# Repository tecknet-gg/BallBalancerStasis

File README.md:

## Overview

A project where I make a cool 3RRS parallel manipulator, and throw a camera underneath and get it to balance a ball. It uses Computer Vision (CV) to locate the ball on the platform, and then the location and velocity vector will be used to calculate the pose of the platform (using Inverse Kinematics) to then push the ball back to the centre. 

I manily made this project since it seemed cool when I saw a couple of people who had made them on YouTube (https://www.youtube.com/watch?v=v4F-cGDGiEw&t=235s), and I (being masochistic), like using PID, so here we are!

The hardware for the most part is done, and the .step file can be found in the hardware folder. Firmware is still in the very early stages, and the balancing software is yet to be written.

With the custom PCB:

Here's the BOM:

| Component             | Function             | Quantity | Price (unit*qty) | Source                                                                                                                                                                     |
| --------------------- | -------------------- | -------- | ---------------- | -------------------------------------------------------------------------------------------------------------------------------------------------------------------------- |
| Raspberry Pi Zero 2 W | Microcontroller      | 1        | £14.15           | https://shop.pimoroni.com/products/raspberry-pi-zero-2-w?variant=42101934587987                                                                                            |
| Pi Camera             | Camera               | 1        | £7               | https://www.amazon.co.uk/dp/B0BZVP3SQW                                                                                                                                     |
| Pi Zero Accessories   | Assorted Accessories | 1        | £8               | https://shop.pimoroni.com/products/zero-adaptor-kit?variant=10462230279 & https://shop.pimoroni.com/products/camera-cable-raspberry-pi-zero-edition?variant=32092803891283 |
| Tie Rod               | Joint                | 10       | £6.99            | https://www.amazon.co.uk/dp/B0DCNGSK9S/?coliid=IMXWIUSGWOUHA&colid=3NYE67N1E05KC&psc=1                                                                                     |
| M3/M4 Assortment      | Strcutural           | ~        | £6.64            | https://amzn.eu/d/07FYMvyj                                                                           |
| DS3218MG              | Servos               | 3        | £29.99           | https://www.amazon.co.uk/dp/B0CY2FVZZM/?coliid=I2RXC2YMY9KN9T&colid=3NYE67N1E05KC&th=1                                                                                     |
| PCA9685               | Servo Driver         | 1        | £4.99            | https://www.amazon.co.uk/dp/B0BKZC1XWR/?coliid=I37WT66U57CC7J&colid=3NYE67N1E05KC&psc=1                                                                                    |
| Power Supply          | Power                | 1        | £16.99           | https://tinyurl.com/2cr9nb7n                                                                                                                                               |
| Shoulder Bolts        | Pin Joints           |          | £4.99            | https://www.amazon.co.uk/dp/B0FDQB24SP?ref=ppx_yo2ov_dt_b_fed_asin_title                                                                                                   |
| PLA                   | Printing Material    | 1        | £13.99           | https://www.amazon.co.uk/dp/B0CD79M1NV?ref=ppx_yo2ov_dt_b_fed_asin_title                                                                                                   |
| 20mm Acrylic Disc     | Platform Disc        | 1        | £3.49            | https://www.amazon.co.uk/dp/B0DJVB82TY/?coliid=I2NBRJSN1CBSC1&colid=3NYE67N1E05KC&psc=1                                                                                    |
| 18AWG Wire            | Wire                 | 2        | £2.90            | https://www.amazon.co.uk/dp/B0CZRGH4CT/?coliid=I36BQ0C4MRSHG2&colid=3NYE67N1E05KC&psc=1                                                                                    |
| PCB             | PCB                 | 5        | £9            | JLCPCB                                                                             |

## Assembly 

You'll want to print out the files under the hardware/compoents directory in the quantities given below:

| Component | Quantity |
| --------- | -------- |
| feet      | 6        |
| standoffs | 6        |
| baseplate | 1        |
| shield    | 1        |
| bottomarm | 3        |
| toparm    | 3        |
| mount     | 3        |
| mountclip | 3        |

With that we start with the base and the feet. For my build, I will add some hotglue to the bottom of the each feet (the side with the smaller radius), to act as a grip. With that, its just a matter of attaching them around the circumference of the base plate. Take care to not atttach them to the holes meant for the standoffs. Use M3x6 or M3x8 screws. They are part of the screw assortment kit in the BOM if you do decide to buy the same. Reference the image below to attach the feet to the correct points.

With the feet in, you'll want to grab your three servos and place them on the mounts as such:

Attach them using M3x10 bolt with a nut on the other end to clamp it in place. Also ensure you have attached the servo horn using the hardware given in the kit. Alternatively you can use an M3x6 bolt to attach the horn to the servo.

Then grab your six standoffs. Follow the same steps you did for the feet (except the hot glue grip), and attach them around the circumference using M3x8 bolts.

Now with your three bottom arms, line up the two holes on the bottom with the two on the servo horn. Using an M3x6 bolt, attach that too to the horn. You won't need a nut since the servo horn is threaded. 

Grab the three top arms now, and attach them to the bottom arms using the M4 shoulder bolt. If you want you can use a standard M4, but I use a tie rod for my build. Secure it on the other side using a lock-nut. Alternatively you could use two nuts twisted toghther tightly with some pliers.

Get your tie rods, and attach the to the top of each arm using an M3x6 or M3x8 Bolt.

You can now attach the electronics shield part to the standoffs. Just use the same M3x8 bolts and attach the shield to the six standoffs.

For the next part, my assembly doesn't have the correct compoenent in it since I don't want to redo it since I'm pretty sure I would screw up the joints, and I really don't want to do that again, so read carefully!

The mount you printed should look something like this:

You'll want to grab the M3x20mm bolt, and put it through one of the holes, then attach a nut. Proceed to screw the bolt in, and thread it through one of the tie rods. When it is on the other side of the tie rod, you'll want to add another nut. Then thread it through the other hole of the mount, and out the other end. At this side, you can use another lock nut to attach it securely. Repeat this for the three mounts. Ensure that the extended bit is pointing inwards and not outwards.

Ok now we can start assembling the electronics. Place the Pi Zero 2 W on the corresponding standoffs, and do the same with the PCA9685. No bolts required. Then place the camera module in its little enclosure. Use the attach the CSI cable to the camera, and the other end to the interface on the Pi Zero 2 (note: you'll probably need another cable specifically for the Pi Zero, one with a thinner end for the Pi Zero's CSI slot, as the stock cable with the camera is intended for the full size Pis). With the three main compoenents in, you can start wiring up the PCA9685 using this diagram (in the hardware directory):

You can then attach the three servos to channels 0, 1 and 2 like in the diagram.

Finally for power, get a barrel jack to screw terminal mount, and just hot glue it somewhere onto the bottom. There's not really any mounting pounts on the screw terminal, so and I didn't really want to model in a recess specifically for that. Attach the two 18AWG wires to the screw terminals, and route it up to the PCA9685, and screw the wires into the corresponding screw terminals on the PCA9685. 

And now we can get onto mounting the platform. Grab your clear acrylic disc and the three mount clip parts. Its not on the 3D assembly, but you'll want first put some M3x6 screws through the main mount, then place the platoform in the recess, and get thread the mount clip onto the bolts, then tighten the screws. You shouldn't need a nut here, but if you end up using a longer bolt, you can. Though the piece is threaded so you shouldn't need to.

If you want to add the IMU mount like I will, you can print out the IMU Mount v4 file (x2), and just attach the IMU (MPU6050) to it, and attach it to the platoform as you did mounting the platform to the the top arm mount!

If you happen to be using the PCB, get yourself the board, solder on the DC Barrel Jack, the Pi Zero 2 W and the PCA9685. Then print out the PCB shield instead of the other shield, and mount the PCB on, and voila. Wire up the camera the same. You can wire the IMU into the I2C extender of the PCA9685 in both cases of using the PCB and not.

The PCB looks like so if you do decide to get it fabricated:

For assembling this, just desolder the headers from a Pi Zero 2 W, and put them on the underside, and solder that to the PCB. With the PCA9685, just desolder the headers too, and replace with vertical headers and again solder to the board, and you can place it on the corresponding shield! Also add 3mm LEDs if you so wish to :]

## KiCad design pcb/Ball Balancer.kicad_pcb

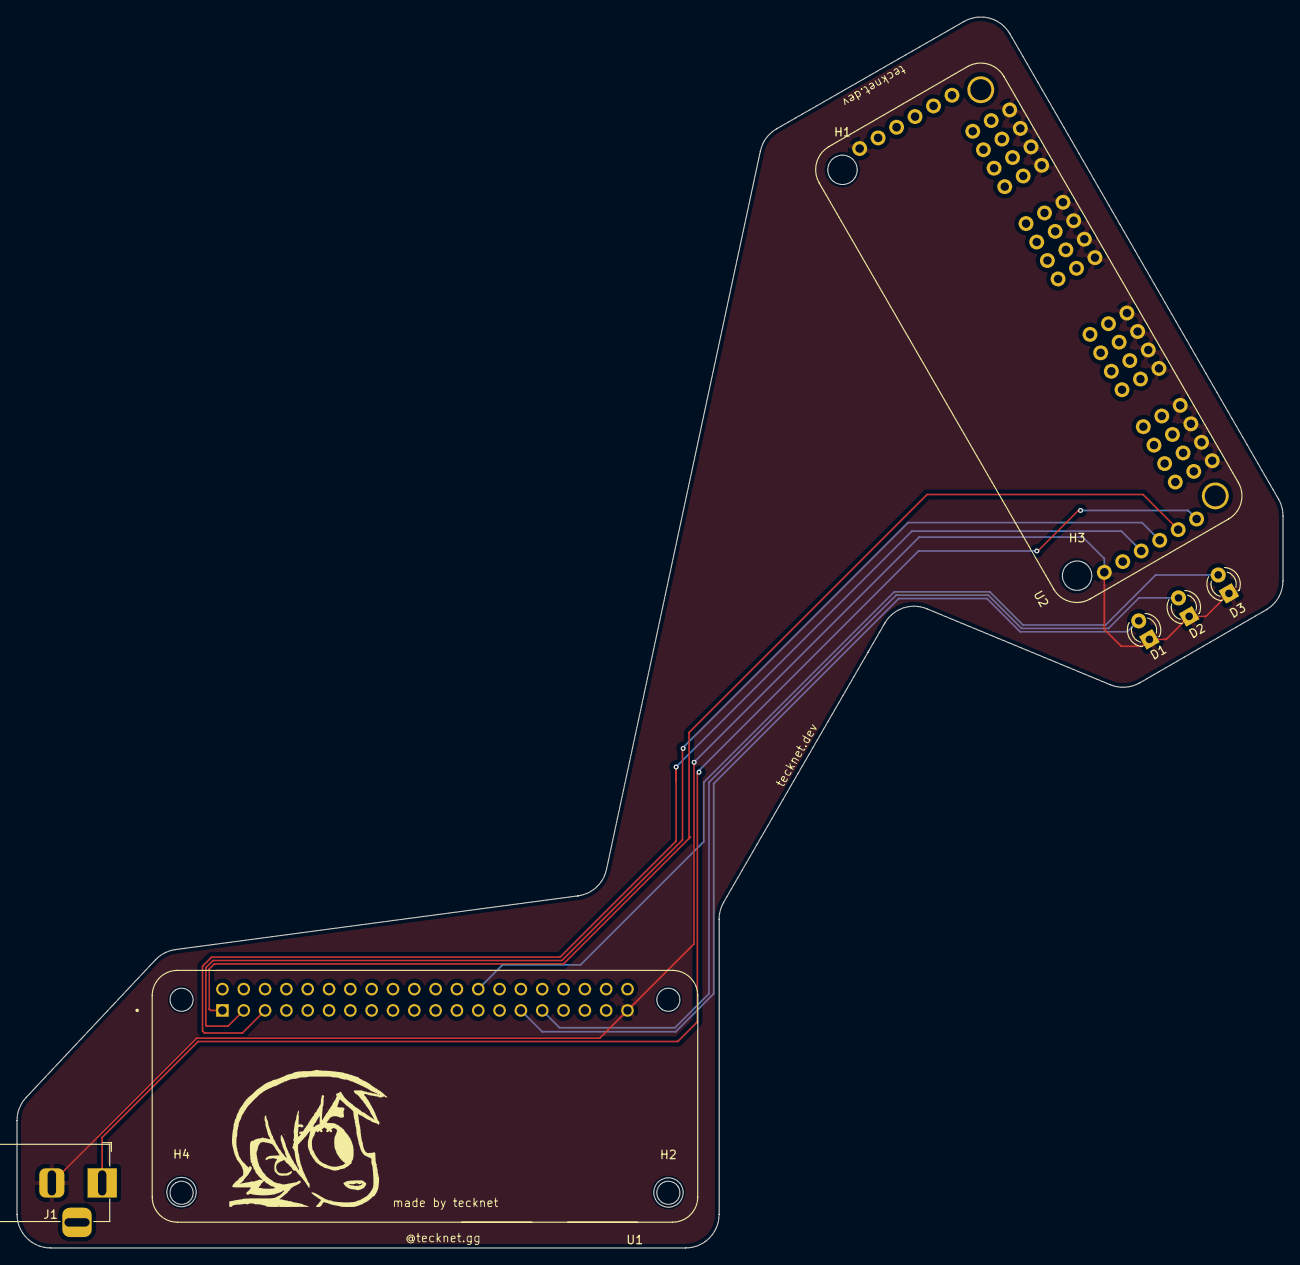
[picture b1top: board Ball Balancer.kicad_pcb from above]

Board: 2 copper layers, 150.8 x 146.7 mm, 10 parts (0 on the bottom side), 9 nets.

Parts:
D1, D2, D3: LED; LED_D3.0mm
H1, H2, H3, H4: MountingHole; MountingHole_3.5mm
J1: Barrel_Jack_MountingPin; BarrelJack_Horizontal
U1: RASPBERRY_PI_ZERO_2_W; MODULE_RASPBERRY_PI_ZERO_2_W
U2: 815; MODULE_815

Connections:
GND: D1.1 (K), D2.1 (K), D3.1 (K), J1.2, U1.39 (GND_39), U2.GND_1 (GND), U2.GND_2 (GND), U2.GND_3 (GND), U2.GND_4 (GND), U2.GND_5 (GND), U2.GND_6 (GND), U2.GND_7 (GND), U2.GND_8 (GND), U2.GND_9 (GND), U2.GND_10 (GND), U2.GND_11 (GND), U2.GND_12 (GND), U2.GND_13 (GND), U2.GND_14 (GND), U2.GND_15 (GND), U2.GND_16 (GND), U2.GND_17 (GND), U2.GND_18 (GND)
unnamed: D1.2 (A), U1.29 (GPIO5)
unnamed: D2.2 (A), U1.31 (GPIO6)
unnamed: D3.2 (A), U1.26 (GPIO7/SPI_~CE1)
unnamed: U1.3 (GPIO2/SDA1), U2.SDA_1 (SDA), U2.SDA_2 (SDA)
unnamed: U1.5 (GPIO3/SCL), U2.SCL_1 (SCL), U2.SCL_2 (SCL)
unnamed: U2.OE_1 (~OE), U2.OE_2 (~OE)
V+: J1.1, U2.V+_1 (V+), U2.V+_2 (V+), U2.V+_3 (V+), U2.V+_4 (V+), U2.V+_5 (V+), U2.V+_6 (V+), U2.V+_7 (V+), U2.V+_8 (V+), U2.V+_9 (V+), U2.V+_10 (V+), U2.V+_11 (V+), U2.V+_12 (V+), U2.V+_13 (V+), U2.V+_14 (V+), U2.V+_15 (V+), U2.V+_16 (V+), U2.V+_17 (V+), U2.V+_18 (V+)
VCC: U1.1 (3V3_1), U2.VCC_1 (VCC), U2.VCC_2 (VCC)

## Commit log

2026-03-07 created hardware folder
2026-03-08 added .step.zip
    extract the file to get the juicy .step file!
2026-03-08 added bom
2026-03-16 making images dir
2026-03-16 Create test
2026-03-16 added picture
2026-03-16 added pictures to assembly
2026-03-16 added final image
    Updated image source for mount clip in README.
2026-03-20 added the IMU mount
2026-03-20 added imu firmware
2026-03-20 added imu mount instructions
2026-03-22 added pcb shield
2026-03-25 added pcb images
    Added assembly instructions and PCB image for fabrication.
2026-03-25 added pcb files
    sorry stasis reviewers!
